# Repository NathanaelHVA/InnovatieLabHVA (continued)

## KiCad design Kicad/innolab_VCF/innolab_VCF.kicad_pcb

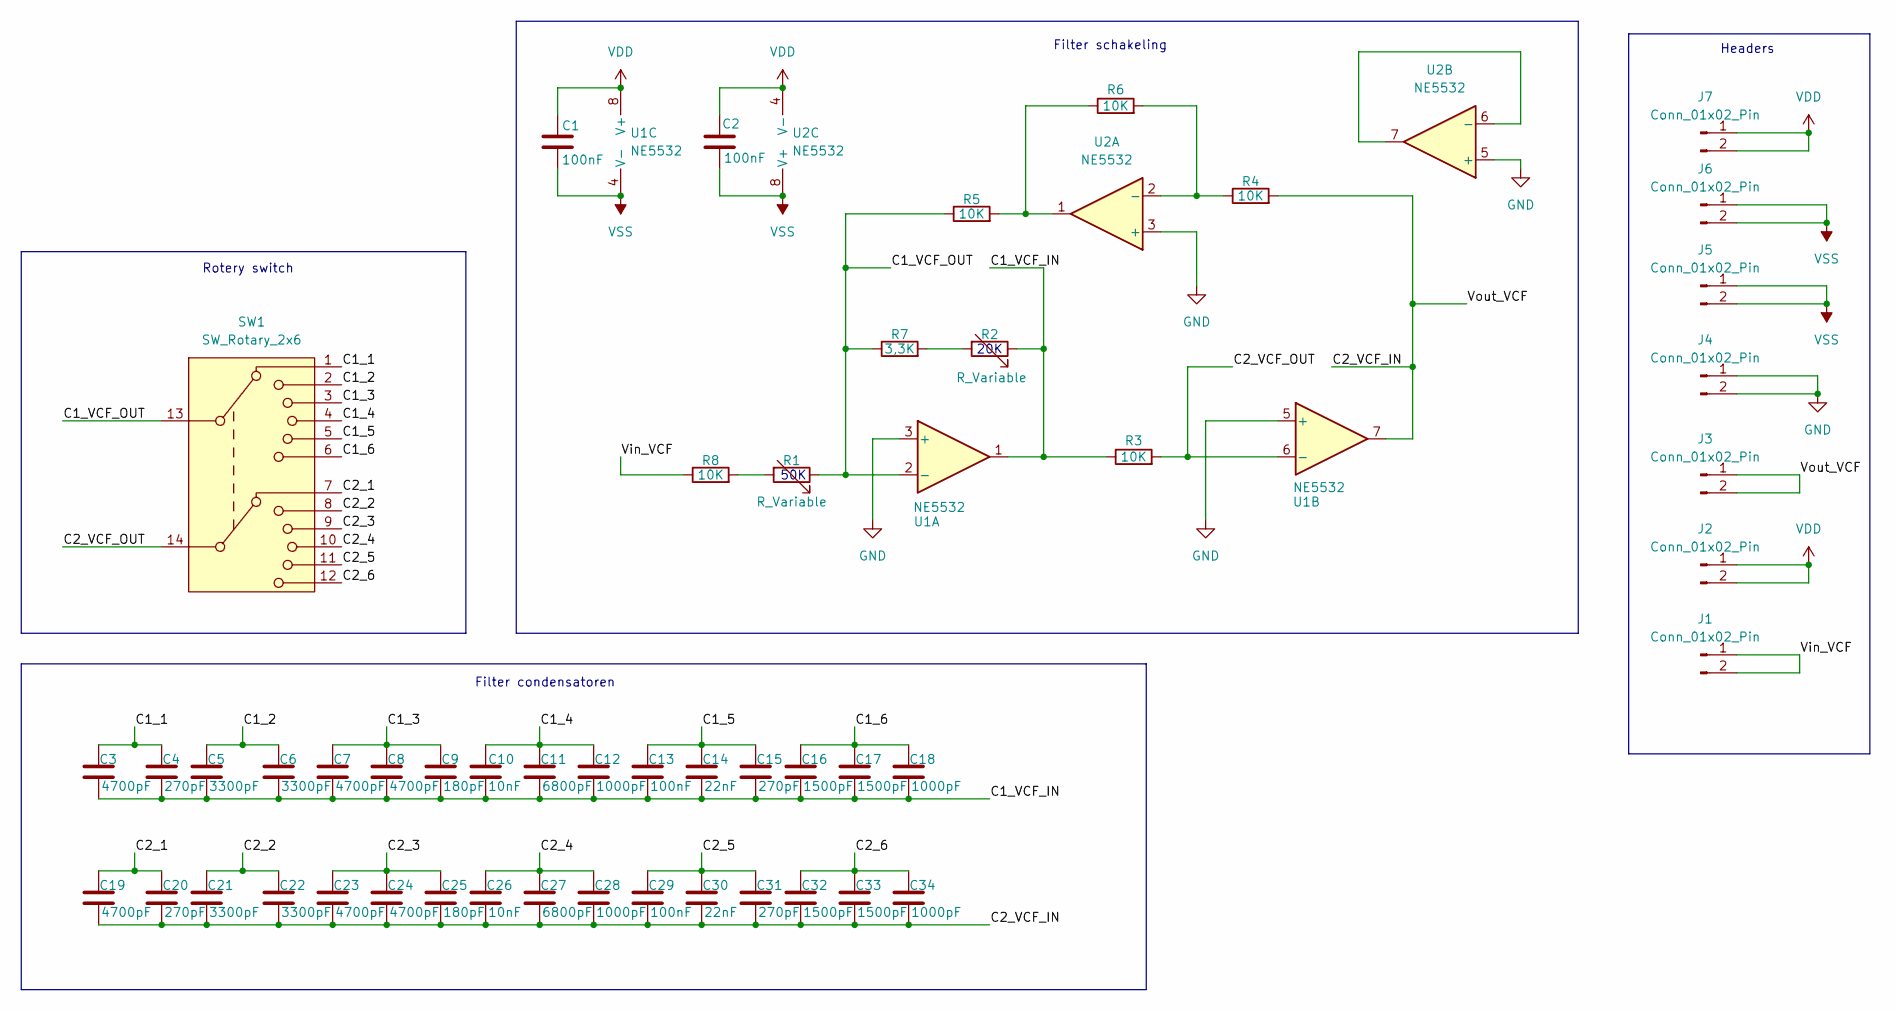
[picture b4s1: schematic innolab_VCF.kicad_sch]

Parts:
C1, C2: 100nF; C_0805_2012Metric_Pad1.18x1.45mm_HandSolder
C3, C7, C8, C19, C23, C24: 4700pF; C_Rect_L7.0mm_W2.0mm_P5.00mm
C4, C15, C20, C31: 270pF; C_0805_2012Metric
C5, C6, C21, C22: 3300pF; C_Rect_L7.0mm_W2.0mm_P5.00mm
C9, C25: 180pF; C_0805_2012Metric
C10, C26: 10nF; C_Rect_L7.0mm_W2.0mm_P5.00mm
C11, C27: 6800pF; C_Rect_L7.0mm_W2.0mm_P5.00mm
C12, C18, C28, C34: 1000pF; C_Rect_L7.0mm_W2.0mm_P5.00mm
C13, C29: 100nF; C_Rect_L7.0mm_W2.0mm_P5.00mm
C14, C30: 22nF; C_Rect_L7.0mm_W2.0mm_P5.00mm
C16, C17, C32, C33: 1500pF; C_Rect_L7.0mm_W2.0mm_P5.00mm
J1, J2, J3, J4, J5, J6, J7: Conn_01x02_Pin; PinHeader_1x02_P2.54mm_Vertical
R1, R2: R_Variable; Potentiometer_Piher_PT-10-H05_Horizontal
R3, R4, R5, R6, R8: 10K; R_0805_2012Metric_Pad1.20x1.40mm_HandSolder
R7: 3,3K; R_0805_2012Metric_Pad1.20x1.40mm_HandSolder
SW1: SW_Rotary_2x6; CK1035
U1, U2: NE5532; SOIC-8_3.9x4.9mm_P1.27mm

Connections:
/C1_1: C3.1, C4.1, SW1.1
/C1_2: C5.1, C6.1, SW1.2
/C1_3: C7.1, C8.1, C9.1, SW1.3
/C1_4: C10.1, C11.1, C12.1, SW1.4
/C1_5: C13.1, C14.1, C15.1, SW1.5
/C1_6: C16.1, C17.1, C18.1, SW1.6
/C1_VCF_IN: C3.2, C4.2, C5.2, C6.2, C7.2, C8.2, C9.2, C10.2, C11.2, C12.2, C13.2, C14.2, C15.2, C16.2, C17.2, C18.2, R2.1, R3.1, U1.1
/C1_VCF_OUT: R1.1, R5.1, R7.1, SW1.13, U1.2 (-)
/C2_1: C19.1, C20.1, SW1.7
/C2_2: C21.1, C22.1, SW1.8
/C2_3: C23.1, C24.1, C25.1, SW1.9
/C2_4: C26.1, C27.1, C28.1, SW1.10
/C2_5: C29.1, C30.1, C31.1, SW1.11
/C2_6: C32.1, C33.1, C34.1, SW1.12
/C2_VCF_IN: C19.2, C20.2, C21.2, C22.2, C23.2, C24.2, C25.2, C26.2, C27.2, C28.2, C29.2, C30.2, C31.2, C32.2, C33.2, C34.2, J3.1, J3.2, R4.2, U1.7
/C2_VCF_OUT: R3.2, SW1.14, U1.6 (-)
/Vin_VCF: J1.1, J1.2, R8.1
GND: J4.1, J4.2, U1.3 (+), U1.5 (+), U2.3 (+), U2.5 (+)
unnamed: R1.2, R8.2
unnamed: R2.2, R7.2
unnamed: R5.2, R6.1, U2.1
unnamed: R4.1, R6.2, U2.2 (-)
unnamed: U2.6 (-), U2.7
VDD: C1.1, C2.1, J2.1, J2.2, J7.1, J7.2, U1.8 (V+), U2.4 (V-)
VSS: C1.2, C2.2, J5.1, J5.2, J6.1, J6.2, U1.4 (V-), U2.8 (V+)

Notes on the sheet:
Filter schakeling
Rotery switch
50K
Filter condensatoren
20K
Headers

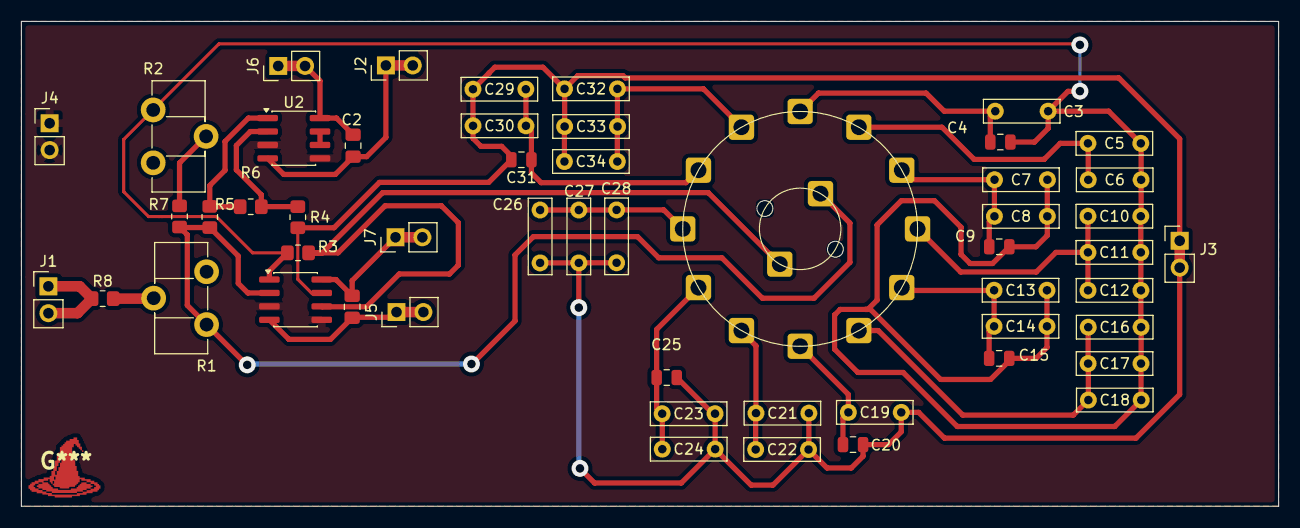
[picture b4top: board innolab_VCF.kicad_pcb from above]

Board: 2 copper layers, 118.9 x 45.8 mm, 52 parts (0 on the bottom side), 25 nets.

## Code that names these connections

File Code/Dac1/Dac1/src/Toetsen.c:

#include <avr/io.h>
#include "toetsen.h"

// Octaafknop op PB4
#define OCTAAF_PORT     PORTB
#define OCTAAF_PIN_bm   PIN4_bm
#define OCTAAF_PINCTRL  PIN4CTRL
#define OCTAAF_BIT      12     

#define TOETS10_BIT     10
#define TOETS10_PORT    PORTC
#define TOETS10_PIN_bm  PIN0_bm
#define TOETS10_PINCTRL PIN0CTRL

static uint8_t  octaaf         = 0;
static uint16_t vorige_sample  = 0; 
static uint16_t vorige_stabiel = 0;   

void toetsen_init(void)
{
    PORTA.DIRCLR = 0xFF;                 // PA0..PA7 als ingang
    PORTB.DIRCLR = 0x0B;                 // PB0, PB1, PB3 als ingang (PB2 = DAC)
    TOETS10_PORT.DIRCLR = TOETS10_PIN_bm;// PC0 als ingang
    OCTAAF_PORT.DIRCLR = OCTAAF_PIN_bm;  // PB4 als ingang

    // Interne pull-downs
    for (uint8_t i = 0; i < 8; i++)
        (&PORTA.PIN0CTRL)[i] = PORT_OPC_PULLDOWN_gc;
    for (uint8_t i = 0; i < 4; i++)
        if (i != 2)                      // PB2 overslaan, die is de DAC-uitgang
            (&PORTB.PIN0CTRL)[i] = PORT_OPC_PULLDOWN_gc;
    TOETS10_PORT.TOETS10_PINCTRL = PORT_OPC_PULLDOWN_gc;
    OCTAAF_PORT.OCTAAF_PINCTRL = PORT_OPC_PULLDOWN_gc;
}

// Alle knoppen in één 16-bit waarde:
// bit 0..7 = PA0..PA7, bit 8, 9, 11 = PB0, PB1, PB3,
// bit 10 = PC0 (toets 10), bit 12 = octaafknop
static uint16_t lees_knoppen(void)
{
    uint16_t a   = PORTA.IN;
    uint16_t b   = PORTB.IN & 0x0B;      // PB0, PB1, PB3 -> bit 8, 9, 11
    uint16_t t10 = (TOETS10_PORT.IN & TOETS10_PIN_bm) ? 1U : 0U;
    uint16_t o   = (OCTAAF_PORT.IN & OCTAAF_PIN_bm) ? 1U : 0U;

    return a | (b << 8) | (t10 << TOETS10_BIT) | (o << OCTAAF_BIT);
}

toetsen_event_t toetsen_poll(void)
{
    toetsen_event_t ev = {0, 0};
    uint16_t nu = lees_knoppen();

    // Debounce: alleen accepteren als twee polls na elkaar gelijk zijn
    if (nu == vorige_sample) {
        uint16_t nieuw = nu & ~vorige_stabiel;   // laag-naar-hoog overgangen

        ev.toetsen = nieuw & ((1U << AANTAL_TOETSEN) - 1);

        if (nieuw & (1U << OCTAAF_BIT)) {
            ev.octaaf = 1;
            octaaf = (octaaf >= OCTAAF_MAX) ? 0 : octaaf + 1;
        }

        vorige_stabiel = nu;
    }
    vorige_sample = nu;

    return ev;
}

uint8_t toetsen_octaaf(void)
{
    return octaaf;
}

char toetsen_poort(uint8_t toets)
{
    if (toets < 8)             return 'A';
    if (toets == TOETS10_BIT)  return 'C';
    return 'B';
}

uint8_t toetsen_pin(uint8_t toets)
{
    if (toets < 8)             return toets;
    if (toets == TOETS10_BIT)  return 0;
    return toets - 8;
}

// Gedebounced stand van de noot-toetsen (bit 0 = toets 0, ...), zonder de octaafknop.
// Voor de gate van de envelope generator: ongelijk aan 0 = er is een toets ingedrukt.
uint16_t toetsen_ingedrukt(void)
{
    return vorige_stabiel & ((1U << AANTAL_TOETSEN) - 1);
}

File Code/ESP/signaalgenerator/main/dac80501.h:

/*!
 * \file    dac80501.h
 * \brief   Twee DAC80501 (16 bit, SPI) tegelijk aansturen vanaf een ESP32-S3
 *
 * De SPI-bits worden door de CPU zelf gemaakt met "dedicated GPIO" (pinnen die de CPU
 * direct kan schakelen). Beide DAC's delen SCLK en SYNC en hebben elk een eigen SDIN,
 * dus beide DAC's krijgen in één frame van 24 klokpulsen tegelijk een nieuwe waarde.
 *
 * Bedrading:
 *   GPIO48 = SCLK   -> SCLK van DAC 1 en DAC 2
 *   GPIO47 = SDIN1  -> SDIN van DAC 1
 *   GPIO45 = SDIN2  -> SDIN van DAC 2  (strapping-pin: GEEN pull-up op deze lijn!)
 *   GPIO21 = SYNC   -> SYNC van DAC 1 en DAC 2 (pull-up, zoals eerst)
 *   Zit de RGB-LED van je board op GPIO47 of 48, dan knippert die mee: onschuldig.
 *   SPI2C-pin van elke DAC naar GND (SPI-mode), VDD van de DAC's op 3V3.
 *
 * Frame van 24 bit: SYNC laag, 8 bit registeradres + 16 bit data, SYNC hoog.
 * Data verandert bij de stijgende flank van SCLK, de DAC leest bij de dalende (SPI mode 1).
 *
 * Let op: dac80501_init() en de write-functies moeten op DEZELFDE core draaien
 * (een dedicated-GPIO-bundel hoort bij de core die hem aanmaakt).
 */
#ifndef DAC80501_H
#define DAC80501_H

#include <stdint.h>

/* ---------- pinnen: hier aanpassen ---------- */
#define DAC_PIN_SCLK      48
#define DAC_PIN_SDIN1     47
#define DAC_PIN_SDIN2     0      // strapping-pin: moet laag zijn bij opstarten, dus geen pull-up
#define DAC_PIN_SYNC      21

/* ---------- uitgangsbereik (zelfde als op de XMEGA) ----------
 * Volle schaal = 2,5 V (interne referentie) / (REF_DIV ? 2 : 1) * (BUFF_GAIN ? 2 : 1)
 *   REF_DIV 1, BUFF_GAIN 1 -> 0 ... 2,5 V   (standaard hier)
 *   REF_DIV 1, BUFF_GAIN 0 -> 0 ... 1,25 V
 */
#define DAC_REF_DIV       1
#define DAC_BUFF_GAIN     1

/* ---------- registers ---------- */
#define DAC_REG_GAIN      0x04
#define DAC_REG_DATA      0x08
#define DAC_GAIN_WAARDE   ((uint16_t)((((DAC_REF_DIV) & 1) << 8) | ((DAC_BUFF_GAIN) & 1)))

/*! \brief Pinnen klaarzetten, beide DAC's configureren en op midscale zetten (stilte) */
void dac80501_init(void);

/*! \brief Eén register in beide DAC's schrijven, elk met een eigen waarde */
void dac80501_write_reg2(uint8_t reg, uint16_t data1, uint16_t data2);

/*! \brief Nieuwe uitgangswaarden (0 ... 65535) naar DAC 1 en DAC 2 tegelijk */
static inline void dac80501_write2(uint16_t code1, uint16_t code2)
{
    dac80501_write_reg2(DAC_REG_DATA, code1, code2);
}

#endif // DAC80501_H

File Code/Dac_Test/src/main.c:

/*!
 * \file    main.c
 * \brief   Pure signaalgenerator: 1 of 2 externe DAC80501 (SPI), 4 golfvormen, frequentie intypen
 *
 * Zo werkt het, van typen tot signaal:
 *   1. Jij typt in de terminal bijvoorbeeld 440 + Enter.
 *   2. freq_input_poll() maakt van die tekens een getal in centi-Hz (440 Hz = 44000).
 *   3. setFreq_centihz() rekent dat om naar een "stap" per sample (vco_step).
 *   4. Een timer (TCC0) tikt FS keer per seconde. In die ISR doen we elke tik:
 *          fase += stap  ->  waarde opzoeken in de golftabel  ->  naar de DAC sturen
 *      Een grote stap = de golf wordt sneller doorlopen = hogere frequentie.
 *
 * Wat je kunt instellen:
 *   - aantal DAC's (1 of 2)  : DAC_AANTAL in dac80501.h (of -DDAC_AANTAL=2)
 *   - golfvorm per VCO       : VCO1_GOLF en VCO2_GOLF hieronder
 *   - toonhoogte van VCO 2   : VCO2_RATIO_Q8 hieronder
 *   - frequentie             : intypen in de terminal, of START_FREQ_CENTIHZ voor bij het opstarten
 *
 * Pinnen: zie dac80501.h (SCLK = PD7, SDIN = PD5, SYNC DAC 1 = PD4, SYNC DAC 2 = PF4)
 */

#define F_CPU 32000000UL               // vóór de includes, één keer (klok gaat naar 32 MHz)

#include <avr/io.h>
#include <avr/interrupt.h>
#include <util/atomic.h>
#include <stdio.h>
#include <stdint.h>
#include <math.h>

#include "serialF0.h"
#include "dac80501.h"
#include "freq_input.h"

/* ---------- instellingen ---------- */

// Samplefrequentie van de VCO's. Per sample gaan er twee SPI-frames van 24 bit over de bus
// (3 us) en de ISR zelf kost ongeveer 9 us (geschat uit de assembly, niet gemeten).
// Bij 100 kHz is de CPU dan bijna vol (10 us per sample); 90 kHz is nog net werkbaar.
// (Dat geldt voor 2 DAC's. Bij DAC_AANTAL 1 gaat er één frame over de bus en wordt maar één VCO berekend.)
#define FS 90000UL

// 1 = lineair interpoleren tussen twee tabelpunten (veel schoner signaal, kost per DAC ongeveer 1-2 us
//     extra in de ISR, niet gemeten); 0 = gewoon het dichtstbijzijnde tabelpunt (blokkerig, ~37 dB SNR)
#define VCO_INTERPOLATIE 1

// Golfvorm per VCO: GOLF_SINUS, GOLF_BLOK, GOLF_ZAAGTAND of GOLF_DRIEHOEK
#define VCO1_GOLF       GOLF_SINUS
#define VCO2_GOLF       GOLF_ZAAGTAND

// Toonhoogte van VCO 2 t.o.v. VCO 1 in 1/256: 256 = gelijk, 512 = een octaaf hoger, 257 = lichte detune
#define VCO2_RATIO_Q8   256UL

// Frequentie bij het opstarten, in centi-Hz (100000 = 1000,00 Hz)
#define START_FREQ_CENTIHZ  100000UL

/* ---------- afgeleide waarden (niet aanpassen) ---------- */

// De timer telt in hele klokpulsen, dus de echte samplefrequentie wijkt een beetje af van FS
// (32 MHz / 355 = 90140 Hz i.p.v. 90000 Hz). Voor de stap rekenen we met de echte waarde,
// anders klopt de frequentie niet precies.
#define FS_DIV    (F_CPU / FS)         // klokpulsen per sample
#define FS_ECHT   (F_CPU / FS_DIV)     // echte samplefrequentie in Hz

/* ---------- golfvormen en VCO's ---------- */

typedef enum { GOLF_SINUS, GOLF_BLOK, GOLF_ZAAGTAND, GOLF_DRIEHOEK, GOLF_AANTAL } golf_t;

static const char *golf_naam[GOLF_AANTAL] = { "sinus", "blok", "zaagtand", "driehoek" };

static uint16_t golf_tabel[GOLF_AANTAL][256];   // 16-bit tabellen voor de DAC80501

static uint32_t                   vco_phase[2];  // alleen de ISR schrijft hierin
static volatile uint32_t          vco_step[2];
static const uint16_t * volatile  vco_lut[2];

// Tabelwaarde bij een 32-bit fase: bovenste 8 bit = tabelindex, de 8 bit daaronder = fractie
static inline uint16_t lut_waarde(const uint16_t *lut, uint32_t phase) {
#if VCO_INTERPOLATIE
    uint8_t  i  = (uint8_t)(phase >> 24);
    uint8_t  fr = (uint8_t)(phase >> 16);
    uint16_t a  = lut[i];
    uint16_t b  = lut[(uint8_t)(i + 1)];            // na punt 255 weer naar punt 0
    int32_t  d  = (int32_t)b - (int32_t)a;
    return (uint16_t)(a + ((d * fr) >> 8));
#else
    return lut[phase >> 24];
#endif
}

// De sampleklok: elke tik één nieuwe waarde naar elke DAC
ISR(TCC0_OVF_vect) {
    vco_phase[0] += vco_step[0];
    dac80501_write(DAC_EXT1, lut_waarde(vco_lut[0], vco_phase[0]));
#if DAC_AANTAL > 1
    vco_phase[1] += vco_step[1];
    dac80501_write(DAC_EXT2, lut_waarde(vco_lut[1], vco_phase[1]));
#endif
}

// frequentie in centi-Hz (440 Hz = 44000); VCO 2 volgt VCO 1 met VCO2_RATIO_Q8
// stap = f / FS * 2^32  (de fase loopt van 0 tot 2^32 = één periode)
static void setFreq_centihz(uint32_t f_centi) {
    uint32_t s1 = (uint32_t)(((uint64_t)f_centi << 32) / (FS_ECHT * 100UL));
    uint32_t s2 = (uint32_t)(((uint64_t)s1 * VCO2_RATIO_Q8) >> 8);
    ATOMIC_BLOCK(ATOMIC_RESTORESTATE) { vco_step[0] = s1; vco_step[1] = s2; }
}

// golfvorm van een VCO wisselen (vco = 0 of 1)
static void vco_set_golf(uint8_t vco, golf_t golf) {
    ATOMIC_BLOCK(ATOMIC_RESTORESTATE) { vco_lut[vco] = golf_tabel[golf]; }
}

// Een via de seriële poort ingetypte frequentie (bijvoorbeeld "440" + Enter) meteen toepassen
static void serieel_frequentie(void) {
    uint32_t f;
    if (freq_input_poll(&f)) {
        setFreq_centihz(f);
        printf("\nFrequentie: %lu.%02lu Hz\n",
               (unsigned long)(f / 100),
               (unsigned long)(f % 100));
    }
}

static void klok_32mhz(void) {
    OSC.CTRL |= OSC_RC32MEN_bm;
    while (!(OSC.STATUS & OSC_RC32MRDY_bm));
    CCP = CCP_IOREG_gc;
    CLK.CTRL = CLK_SCLKSEL_RC32M_gc;
}

static void golf_init(void) {
    for (int i = 0; i < 256; i++) {
        golf_tabel[GOLF_SINUS][i]    = (uint16_t)(32767.5 + 32767.0 * sin(2 * M_PI * i / 256.0));
        golf_tabel[GOLF_BLOK][i]     = (i < 128) ? 65535 : 0;
        golf_tabel[GOLF_ZAAGTAND][i] = (uint16_t)((uint32_t)i * 65535UL / 255UL);
        golf_tabel[GOLF_DRIEHOEK][i] = (uint16_t)((uint32_t)((i < 128) ? i : 255 - i) * 65535UL / 127UL);
    }
    vco_set_golf(0, VCO1_GOLF);
    vco_set_golf(1, VCO2_GOLF);

    // Timer TCC0 als sampleklok: ISR elke FS_DIV klokpulsen
    TCC0.PER = FS_DIV - 1;
    TCC0.INTCTRLA = TC_OVFINTLVL_HI_gc;
    TCC0.CTRLA = TC_CLKSEL_DIV1_gc;
    PMIC.CTRL |= PMIC_HILVLEN_bm;
}

/* ---------- main ---------- */

int main(void)
{
    klok_32mhz();
    init_stream(F_CPU);
    dac80501_init();           // SPID + de DAC('s) instellen (DAC_AANTAL)
    golf_init();               // tabellen + sampleklok (de ISR schrijft naar de DAC's)
    setFreq_centihz(START_FREQ_CENTIHZ);
    sei();                     // pas hierna kan printf versturen (TX werkt met interrupts)

    printf("\nSignaalgenerator, %u DAC(s)\n", (unsigned)DAC_AANTAL);
    printf("DAC 1: %s", golf_naam[VCO1_GOLF]);
#if DAC_AANTAL > 1
    printf("   DAC 2: %s", golf_naam[VCO2_GOLF]);
#endif
    printf("\nTyp een frequentie (440 of 261.63) + Enter\n");

    while (1) {
        serieel_frequentie();  // niet-blokkerend: kijkt of er nieuwe tekens zijn
    }
}
